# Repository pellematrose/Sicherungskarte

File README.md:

# Sicherungskarte
Sicherungskarte für 24V-Systeme, zum Absichern von Lasten und Stromkreisen.

---
## 🔧 Gedachte Verwendung
An die oberen Schraubklemmen wird die Versorgungsspannung angeschlossen.  
An die unteren Schraubklemmen wird die Last bzw. der Stromkreis der abgesichert werden soll, angeschlossen.  

Die **maximale** Sicherungsgröße beträgt **10A!**  

---

## 📏 Technische Daten
- Versorgungsspannung: 24V (+-20%)
- Laststrom: 10A max
- PCB Maße: 56 mm x 52 mm

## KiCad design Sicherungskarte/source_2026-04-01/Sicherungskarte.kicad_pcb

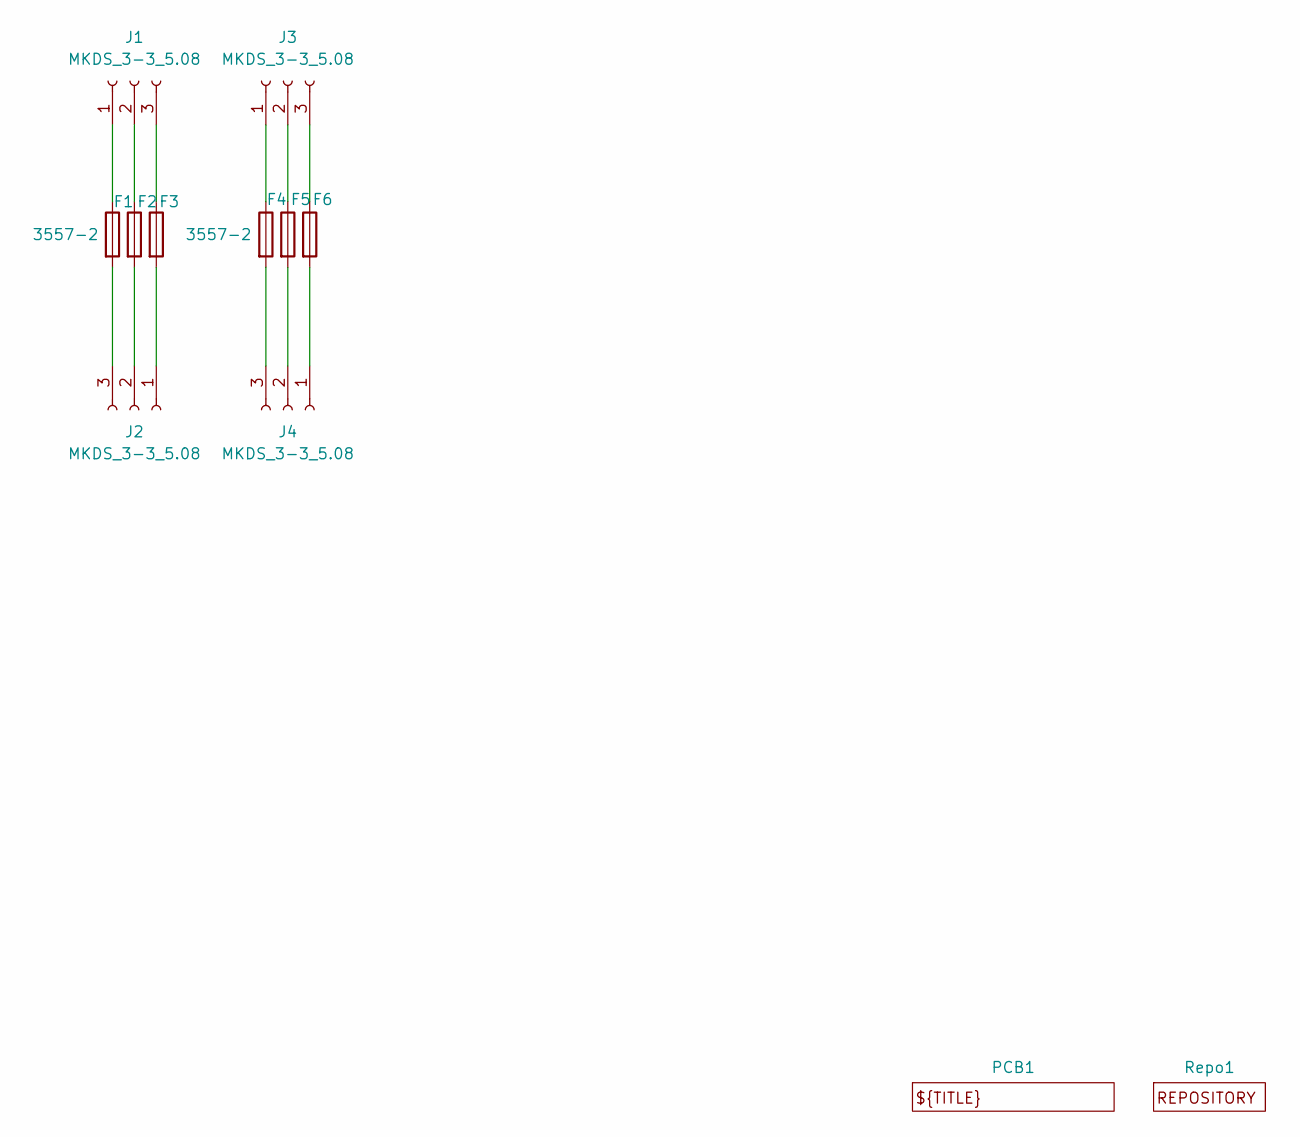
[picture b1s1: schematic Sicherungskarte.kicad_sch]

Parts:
F1, F2, F3, F4, F5, F6: 3557-2; Fuse Holder Littelfuse ATOF 287; Digikey 36-3557-2-ND
J1, J2, J3, J4: MKDS_3-3_5.08; MKDS_3_3_508; Digikey 277-1028-ND
PCB1: _PCB
Repo1: _Repository

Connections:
unnamed: F1.1, J1.1
unnamed: F2.1, J1.2
unnamed: F3.1, J1.3
unnamed: F3.2, J2.1
unnamed: F2.2, J2.2
unnamed: F1.2, J2.3
unnamed: F4.1, J3.1
unnamed: F5.1, J3.2
unnamed: F6.1, J3.3
unnamed: F6.2, J4.1
unnamed: F5.2, J4.2
unnamed: F4.2, J4.3

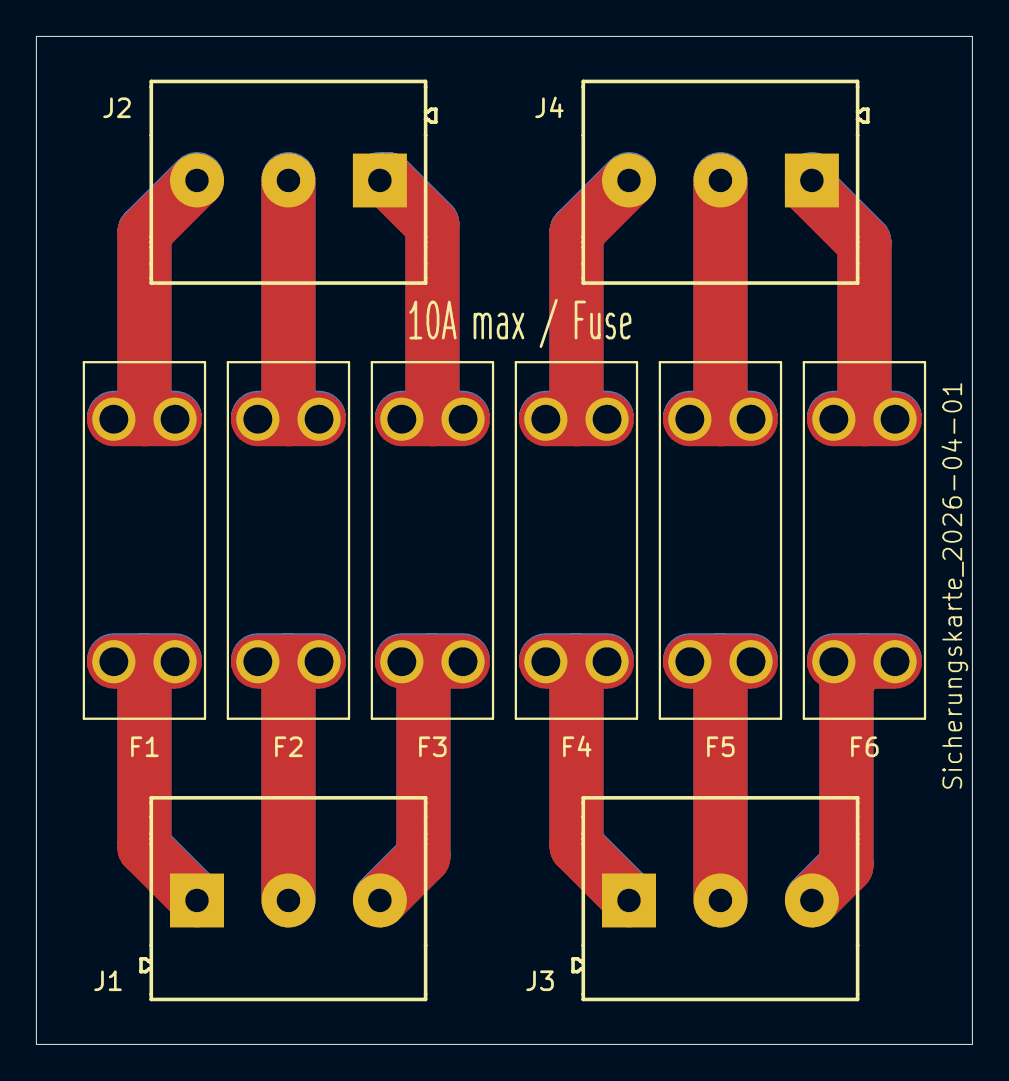
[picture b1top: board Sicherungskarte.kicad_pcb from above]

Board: 2 copper layers, 52.0 x 56.0 mm, 12 parts (1 on the bottom side), 12 nets.

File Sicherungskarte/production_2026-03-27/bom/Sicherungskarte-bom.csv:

"Refs","Value","Footprint","Qty","DNP"
"F1-F6","3557-2","_PS_LIB_CON:Fuse Holder Littelfuse ATOF 287","6",""
"J1-J4","MKDS_3-3_5.08","_PS_LIB_CON:MKDS_3_3_508","4",""

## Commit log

2026-04-05 final version

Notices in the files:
Sicherungskarte/source_2026-03-27/Sicherungskarte.kicad_sch:
Licensed under CERN-OHL-S v2
© 2026 Per-Simon Saal
Sicherungskarte/source_2026-04-01/Sicherungskarte.kicad_pcb:
CERN-OHL-S v2
